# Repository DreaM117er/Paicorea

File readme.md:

# Paicorea

|||
|--|--|
|||

## 說明

Paicorea是一把專門為我而設計的分離式機械鍵盤，目的是為了讓鍵盤可以達到極度輕薄，又可以搭載`TPS43`這張由`Azoteq`公司生產製造的觸控板，滿足我的日常生活而使用。

它可以根據自己的需求選擇是否觸控板作為滑鼠使用；鍵盤按鍵則是使用`Kailh`生產製造的`PG1316S`作為它「目前」的按鍵使用，往後不排除會設計另一種機械鍵軸的版本來給自己做使用。

鍵盤的最初設計是像[AZCARD](https://github.com/palette-system/azcard)、[Bayleaf](https://kbd.news/Bayleaf-2610.html)、[Makefive](https://github.com/mikeholscher/zmk-config-mikefive)等一樣搭載`PG1316S`鍵軸的鍵盤都是以本體PCB作為底板壓縮厚度到3mm左右，但因為本人——也就是我自己，非常不喜歡使用無線設備（電池安全問題）的原因，一定得在鍵盤上搭載分離式鍵盤常見的`3.5mm TRRS座`，而我在這部分花了很多時間尋找能使用的零件，最後找到`PJ-381B`、`PJ-381C`、`PJ-399`等3款可以使用的沉板型號，再根據Datasheet跟3D設計，選擇了`PJ-381B`來使用。

在不想向下更換`2.5mm TRRS座`的前提下，很可惜地我只能將鍵盤厚度壓縮至5.5mm左右，但整體的結構讓我相當滿意。

使用`RP2040 Core-A`的原因——它跟用排線分離設計的`RP2040-Tiny`不同，我可以直接在PCB上拉USB2.0使用的USB-C口接線接在`RP2040 Core-A`上達到分離MCU跟USB-C的目的，而不用而外設計一個專門放置排線跟分離板的位置，而且又是厚度只有5.5mm的空間內。

最終從MCU——RP2040 Core-A（Raspberry Pi）中取Pi（π，Pai同音）、Core-A（corea），Paicorea就這麼誕生了。

## 使用材料

|名稱|規格|數量|備註|
|--|--|--|--|
|MCU|RP2040 Core-A|2|[Aliexpress Link](https://es.aliexpress.com/item/1005006101790601.html?channel=twinner)|
|Type-C母座|TYPE-C 16P CB1.6|2|沉板1.6mm|
|TRRS母座|PJ-381B|2|-|
|二極體|1N4148 `SOD-123`|42|-|
|貼片電阻|5.1K、`0603`|4|焊接後可支援C2C|
|鍵軸|Kailh PG1316S|42|-|
|鍵帽|適用PG1316S、`1u`大小|42|推薦用買的，3D列印需`留意邊角`圓弧|
|貼片銅柱|MAC8 TH0.8-2.0-M2（2.0）|16|-|
|貼片銅柱|MAC8 TH1.6-2.0-M2（2.0）|8|-|
|M2螺絲|牙長5mm、頭部`小於`ø4.2mm|24|-|
|矽膠自黏腳貼|ø8mm、厚度0.5-1.0mm|-|根據自己所需決定數量|
|緩衝墊|厚度0.5-0.8mm|-|矽膠或Poron等緩衝材料；需要裁切大小，請自行判斷需要多大面積|
|PVC板材|厚度0.8mm|-|觸控板面用，`A4`大小即可，需要裁切|
|0.5mm FFC排線座|6Pin|1|選配，安裝觸控板才需要|
|0.5mm FFC軟排線|6Pin、50mm、`AA同向`|1|選配，安裝觸控板才需要|
|觸控板|Azoteq TPS43-201A-S|1|選配|
|貼片LED燈|SK6805-2427（Micro）|6|選配，裝飾燈|

## 鍵盤結構

|||
|--|--|

|順序|部件|厚度（mm）|備註|
|--|--|--|--|
|1|上蓋-A（Cover-A）、觸控板邊框-A（Track-A）|1.6|有無觸控板做選擇|
|2|上蓋-B（Cover-B）、觸控板邊框-B（Track-B）|0.8|有無觸控板做選擇|
|3|定位板（Plate）|0.8|-|
|4|間隙空間板（Body）|1.6|-|
|5|核心電路板（Main）|1.6|-|
|6|緩衝層（Frame）|0.5-0.8|自行裁切或使用電路板層都可|
|7|底板（Bottom）|0.8|-|

## 使用工具

||名稱|使用場合|備註|
|--|--|--|--|
|1|電烙鐵|基本電路板焊接|修正焊錫使用，推薦使用K頭（刀頭）|
|2|熱風槍或加熱台|進階電路板焊接|擇一使用即可|
|3|針筒裝錫膏|進階電路板焊接||
|4|剪刀及美工刀|裁切膠帶及塑料板材||
|5|超薄超黏雙面膠|粘貼固定觸控板用|0.13-0.15mm厚度的即可|
|6|對應電路板顏色的簽字筆|邊框填色使用|可不需使用|
|7|防靜電金屬鑷子|進階電路板焊接、測試、精密操作||
|8|精密螺絲起子|-|對應螺絲規格使用|
|9|平口老虎鉗|分離拼接電路板時使用||
|10|銼刀|打磨電路板邊框時用||
|11|皮革打洞器|裁切矽膠墊使用|需要打ø4-4.5mm的孔|
|12|鉛筆或原子筆|裁切PVC塑膠板時使用||
|13|3秒膠或AB膠|固定層板使用||

## 組裝說明

### 注意事項

- 務必將所有元件都焊接在同一面。
- 焊接MCU、二極體、鍵軸及LED燈等... 都務必都要進行測試再做下一步動作。
- 只要有安裝方向的元件都會標示在電路板上，反之沒有安裝方向的元件什麼都不會標記。
- MCU上的THT焊盤孔用作定位使用。
- 使用焊接工具時務必注意安全，小心燙傷。

### 安裝順序

|圖示|說明|
|--|--|
||首先將`MCU`、`USB-C`接口、`5.1K`電阻及`FFC`排線座焊接好。|
||連接電腦測試MCU的狀態，如果順利接通MCU的話，MCU上面的`橘紅色LED燈`會閃爍。|
||請根據RP2040的燒錄方式將韌體燒錄至MCU，成功的話LED燈會亮，還有VIAL會成功讀取到鍵盤。|
||再來焊接TRRS座。|
||接著按照順序將`1N4148`及`PG1316S`焊接起來，PG1316S的燈光孔是可以容下1N4148的，務必將二極體包覆在軸燈燈孔裡面。|
||然後將貼片銅柱（`MAC8 TH1.6-2.0-M2`）焊接上去。|
||接著將另一側鍵盤也焊好。|
||再來將底板（Bottom）的貼片銅柱（`MAC8 TH0.8-2.0-M2`）也焊接固定好。|
||接著依照底板（Bottom）、緩衝層（Frame）、電路板（Main）、間隙（Body）、定位板（Plate）的順序將鍵盤疊好，再把鍵盤外側的螺絲鎖上去固定。|
||將Cover-A、Cover-B、Track-A、Track-B用工具剝下來。|
||然後將其中一側的Cover蓋起來用螺絲鎖好，完成其中一邊，如果不需要安裝觸控板就把兩側鍵盤都鎖上Cover就完成了。|
||觸控板的部分可以選擇使用列印或自己切觸控板Cover。|
||首先將觸控板上的3M貼紙撕下來貼在8mm的PVC板材上後裁切下來，再把多餘的邊切除。|
||好了之後將Track-A固定好，貼上超黏雙面膠。|
||一樣切除多餘的膠。|
||撕下膠的另一面之後，將A、B合併在一起。|
||接上排線，稍微彎折收納一下排線。|
||鎖上螺絲。|
||然後翻到背面貼上腳貼或自行DIY上Tending。|
||安裝鍵帽之後就完成啦。|

## 參考資料

### 鍵盤
- [AZCARD](https://github.com/palette-system/azcard)：結構部分及銅柱元件參照。
- [Makefive](https://github.com/mikeholscher/zmk-config-mikefive)：結構部分。
- [Bayleaf](https://kbd.news/Bayleaf-2610.html)：結構部分。
- [Corne v4](https://github.com/foostan/crkbd)：TRRS連接座、PCB走線參照。
- [X：おおやけハジメ](https://x.com/digitarhythm)——[未完成"V1"](https://x.com/digitarhythm/status/1908885665695363132)：
PCB走線參照。

### 部落格、網頁、參考說明書
- [Holykeeb](https://holykeebs.com/)、[Holykeeb.Docs](https://docs.holykeebs.com/guides/touchpad-module/)。
- [74th Blog](https://74th.hateblo.jp/entry/testing-TPS43-201A-S)
- [Reddit: mikefive, a Kailh PG1316 keyboard](https://www.reddit.com/r/ErgoMechKeyboards/comments/1cfg3vr/mikefive_a_kailh_pg1316_keyboard/)
- [KBD.News](https://kbd.news/)

### 規格書
- PJ-381B、PJ-381-C、PJ-399。
- TYPE-C 16P CB1.6。
- MAC8 THXX-XX-M2。
- SK6805-2427。
- Kailh PG1316S & Keycap。
- Azoteq TPS43-201A-S。

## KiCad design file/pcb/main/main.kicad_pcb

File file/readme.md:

## 注意事項

- 公差設定0.05mm。
- 3D模型由於沒有變更太多東西，相容性不影響，因此我就沒有更新新的上去了。
- 結構為標準電路板堆疊，因此才能夠將鍵盤壓縮至10mm以內。
- 底板經過Prototype測試，厚度不允許從1.6mm降低至0.8mm，TRRS線會摩擦桌面，實際使用上會有問題。
- 裁切能力有限的夥伴，請一律定製電路板外殼來製作鍵盤，厚度不會差異太多。

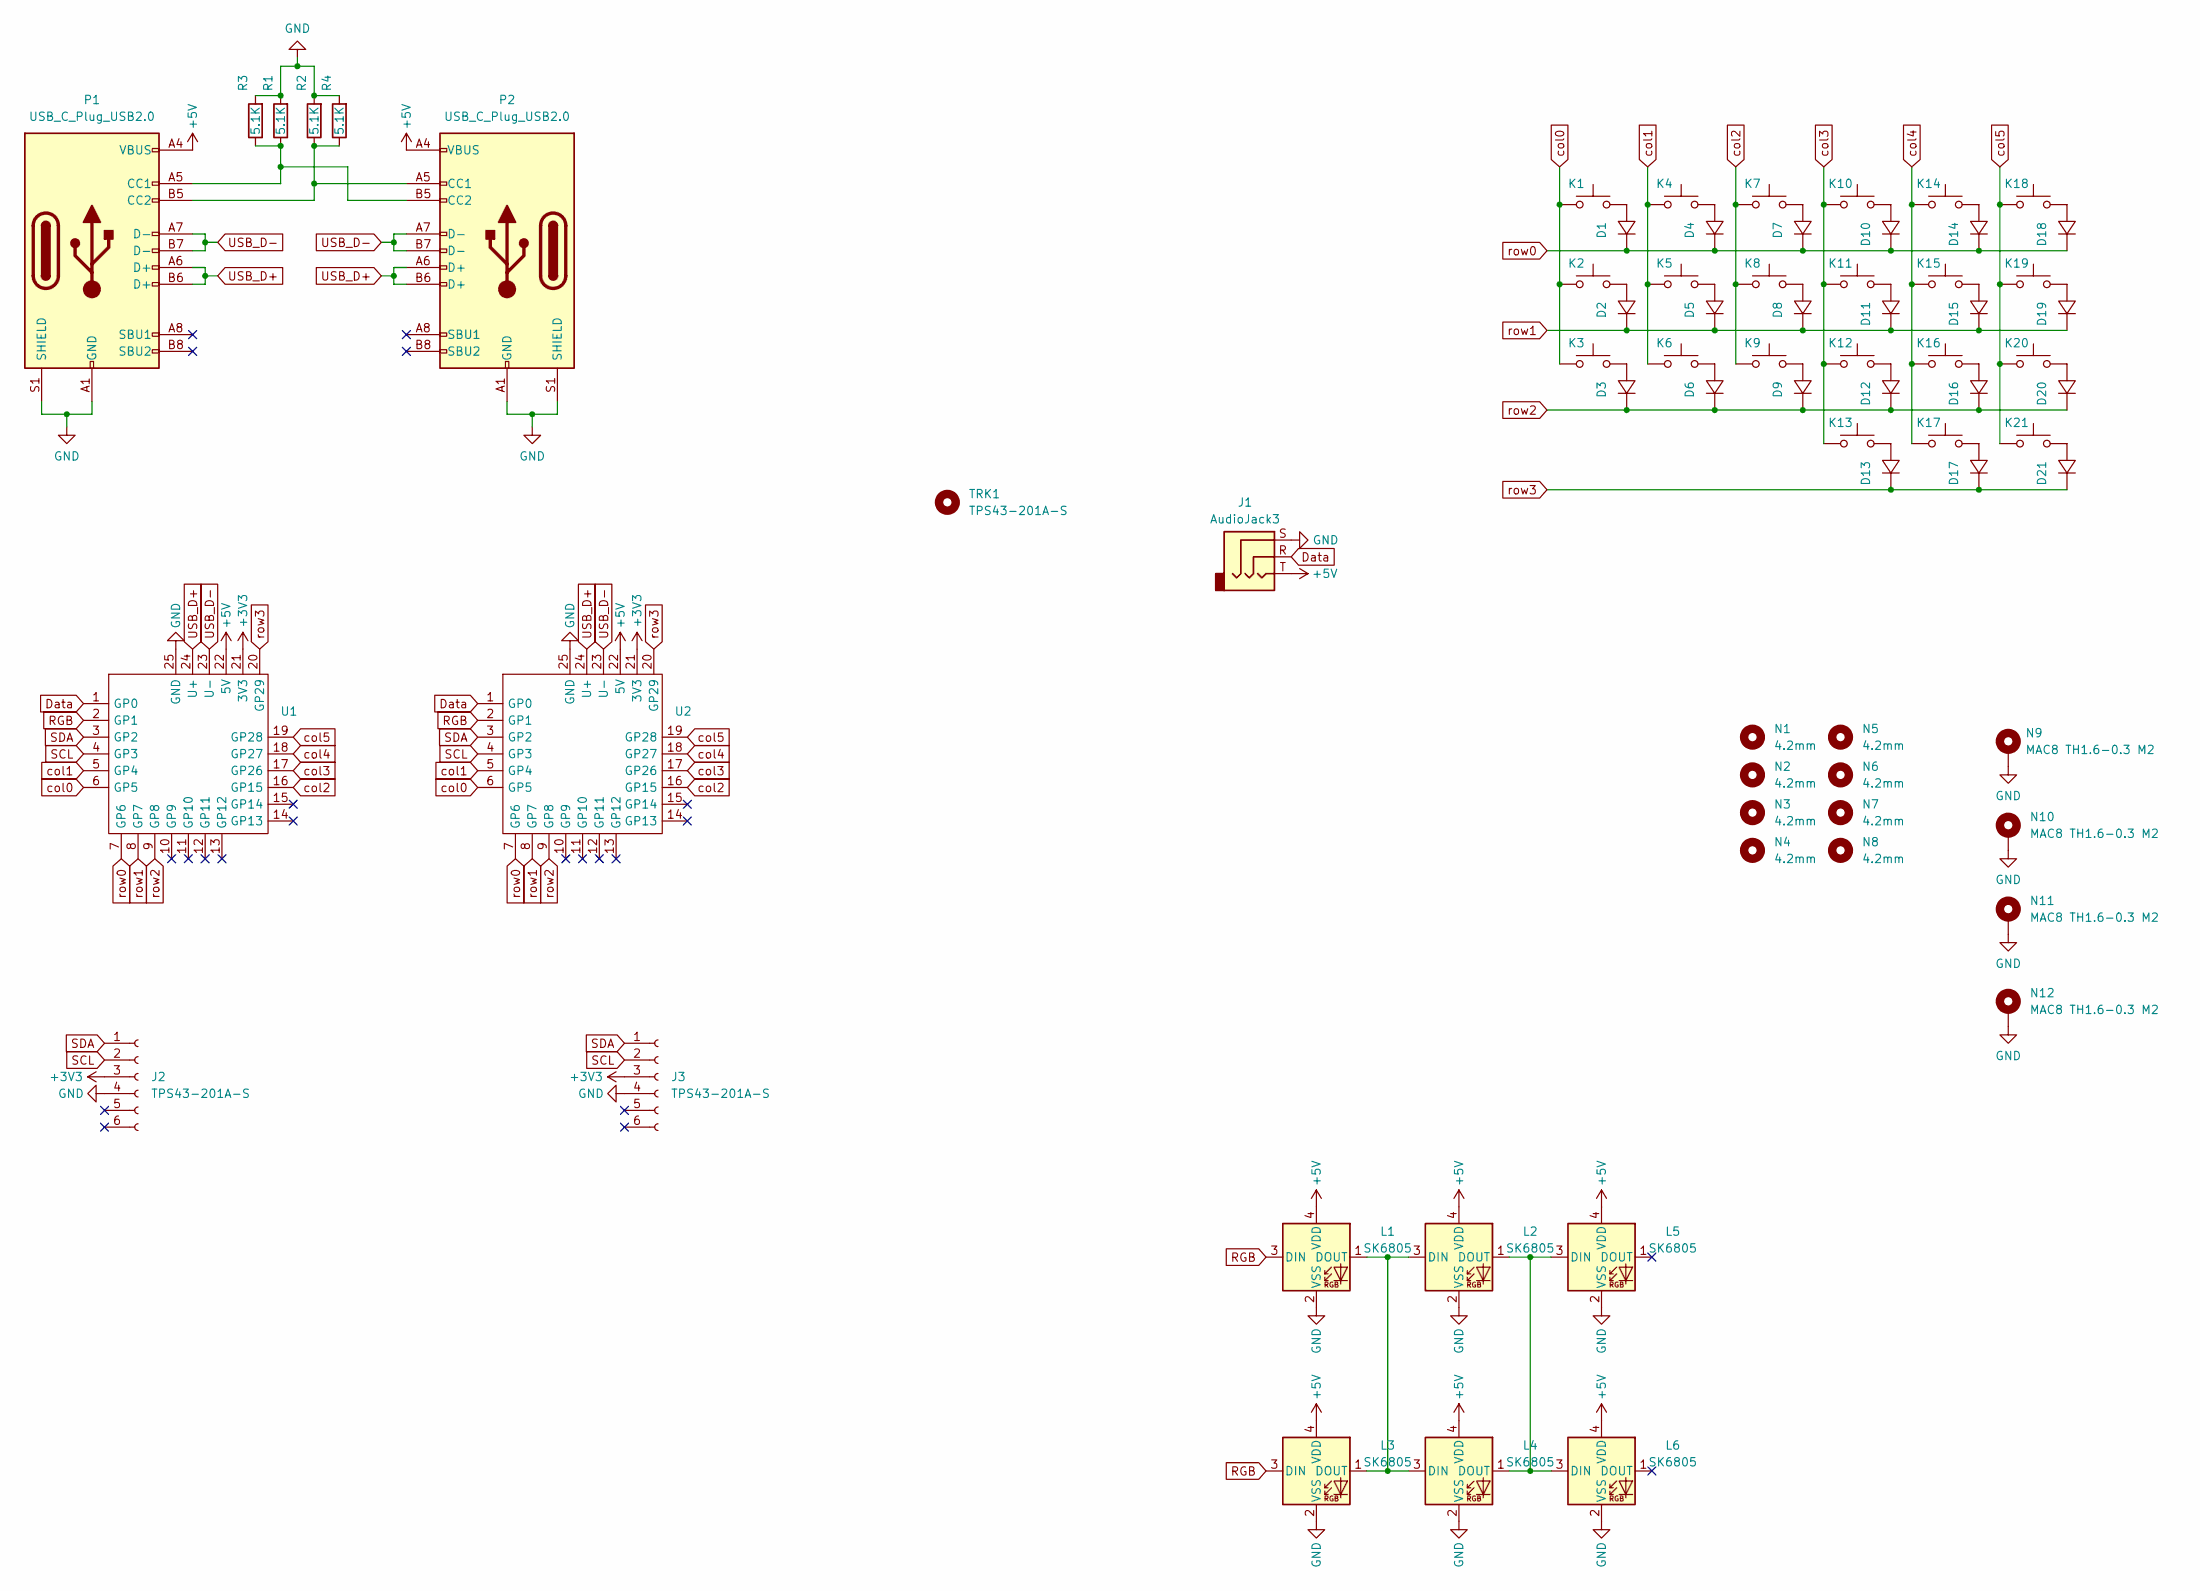
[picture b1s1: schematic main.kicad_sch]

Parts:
D1, D2, D3, D4, D5, D6, D7, D8, D9, D10, D11, D12, D13, D14, D15, D16, D17, D18, D19, D20, D21: 1N4148_SMD; D_SOD-123_dual
J1: AudioJack3; TRRS-PJ-381-BB_6P_Dual
J2, J3: TPS43-201A-S; Hirose_FH12-6S-0.5SH_1x06-1MP_P0.50mm_Horizontal
K1, K2, K3, K4, K5, K6, K7, K8, K9, K10, K11, K12, K13, K14, K15, K16, K17, K18, K19, K20, K21: PG1316S; SW_Kailh_PG1316S_1.00u_Dual2
L1, L2, L3, L4, L5, L6: SK6805; LED_SK6805_PLCC4_2.4x2.7mm_P1.3mm
N1, N2, N3, N4, N5, N6, N7, N8: 4.2mm; MAC8_TH0816-XX-M2-NPTHhole
N9, N10, N11, N12: MAC8 TH1.6-0.3 M2; MAC8_TH0816-XX-M2-Dual_Pad
P1, P2: USB_C_Plug_USB2.0; USB_C_16P_MID_MOUT_SR_Molex
R1, R2, R3, R4: 5.1K; R_0603_1608Metric
TRK1: TPS43-201A-S; Azoteq_TPS43_201A_S
U1, U2: MCU_RP2040_CoreA_SMD; MCU_RP2040CoreA_SMD

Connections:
+3V3: J2.3, J3.3, U1.21 (3V3), U2.21 (3V3)
+5V: J1.T, L1.4 (VDD), L2.4 (VDD), L3.4 (VDD), L4.4 (VDD), L5.4 (VDD), L6.4 (VDD), P1.A4 (VBUS), P1.A9 (VBUS), P1.B4 (VBUS), P1.B9 (VBUS), P2.A4 (VBUS), P2.A9 (VBUS), P2.B4 (VBUS), P2.B9 (VBUS), U1.22 (5V), U2.22 (5V)
Data: J1.R, U1.1 (GP0), U2.1 (GP0)
GND: J1.S, J2.4, J3.4, L1.2 (VSS), L2.2 (VSS), L3.2 (VSS), L4.2 (VSS), L5.2 (VSS), L6.2 (VSS), N9.1, N10.1, N11.1, N12.1, P1.A1 (GND), P1.A12 (GND), P1.B1 (GND), P1.B12 (GND), P1.S1 (SHIELD), P2.A1 (GND), P2.A12 (GND), P2.B1 (GND), P2.B12 (GND), P2.S1 (SHIELD), R1.2, R2.2, R3.2, R4.2, U1.25 (GND), U2.25 (GND)
unnamed: D1.2, K1.2
unnamed: D2.2, K2.2
unnamed: D3.2, K3.2
unnamed: D4.2, K4.2
unnamed: D5.2, K5.2
unnamed: D6.2, K6.2
unnamed: D7.2, K7.2
unnamed: D8.2, K8.2
unnamed: D9.2, K9.2
unnamed: D10.2, K10.2
unnamed: D11.2, K11.2
unnamed: D12.2, K12.2
unnamed: D13.2, K13.2
unnamed: D14.2, K14.2
unnamed: D15.2, K15.2
unnamed: D16.2, K16.2
unnamed: D17.2, K17.2
unnamed: D18.2, K18.2
unnamed: D19.2, K19.2
unnamed: D20.2, K20.2
unnamed: D21.2, K21.2
unnamed: L1.1 (DOUT), L2.3 (DIN), L3.1 (DOUT), L4.3 (DIN)
unnamed: L2.1 (DOUT), L4.1 (DOUT), L5.3 (DIN), L6.3 (DIN)
unnamed: P1.A5 (CC1), P2.B5 (CC2), R1.1, R3.1
unnamed: P1.B5 (CC2), P2.A5 (CC1), R2.1, R4.1
RGB: L1.3 (DIN), L3.3 (DIN), U1.2 (GP1), U2.2 (GP1)
SCL: J2.2, J3.2, U1.4 (GP3), U2.4 (GP3)
SDA: J2.1, J3.1, U1.3 (GP2), U2.3 (GP2)
USB_D+: P1.A6 (D+), P1.B6 (D+), P2.A6 (D+), P2.B6 (D+), U1.24 (U+), U2.24 (U+)
USB_D-: P1.A7 (D-), P1.B7 (D-), P2.A7 (D-), P2.B7 (D-), U1.23 (U-), U2.23 (U-)
col0: K1.1, K2.1, K3.1, U1.6 (GP5), U2.6 (GP5)
col1: K4.1, K5.1, K6.1, U1.5 (GP4), U2.5 (GP4)
col2: K7.1, K8.1, K9.1, U1.16 (GP15), U2.16 (GP15)
col3: K10.1, K11.1, K12.1, K13.1, U1.17 (GP26), U2.17 (GP26)
col4: K14.1, K15.1, K16.1, K17.1, U1.18 (GP27), U2.18 (GP27)
col5: K18.1, K19.1, K20.1, K21.1, U1.19 (GP28), U2.19 (GP28)
row0: D1.1, D4.1, D7.1, D10.1, D14.1, D18.1, U1.7 (GP6), U2.7 (GP6)
row1: D2.1, D5.1, D8.1, D11.1, D15.1, D19.1, U1.8 (GP7), U2.8 (GP7)
row2: D3.1, D6.1, D9.1, D12.1, D16.1, D20.1, U1.9 (GP8), U2.9 (GP8)
row3: D13.1, D17.1, D21.1, U1.20 (GP29), U2.20 (GP29)

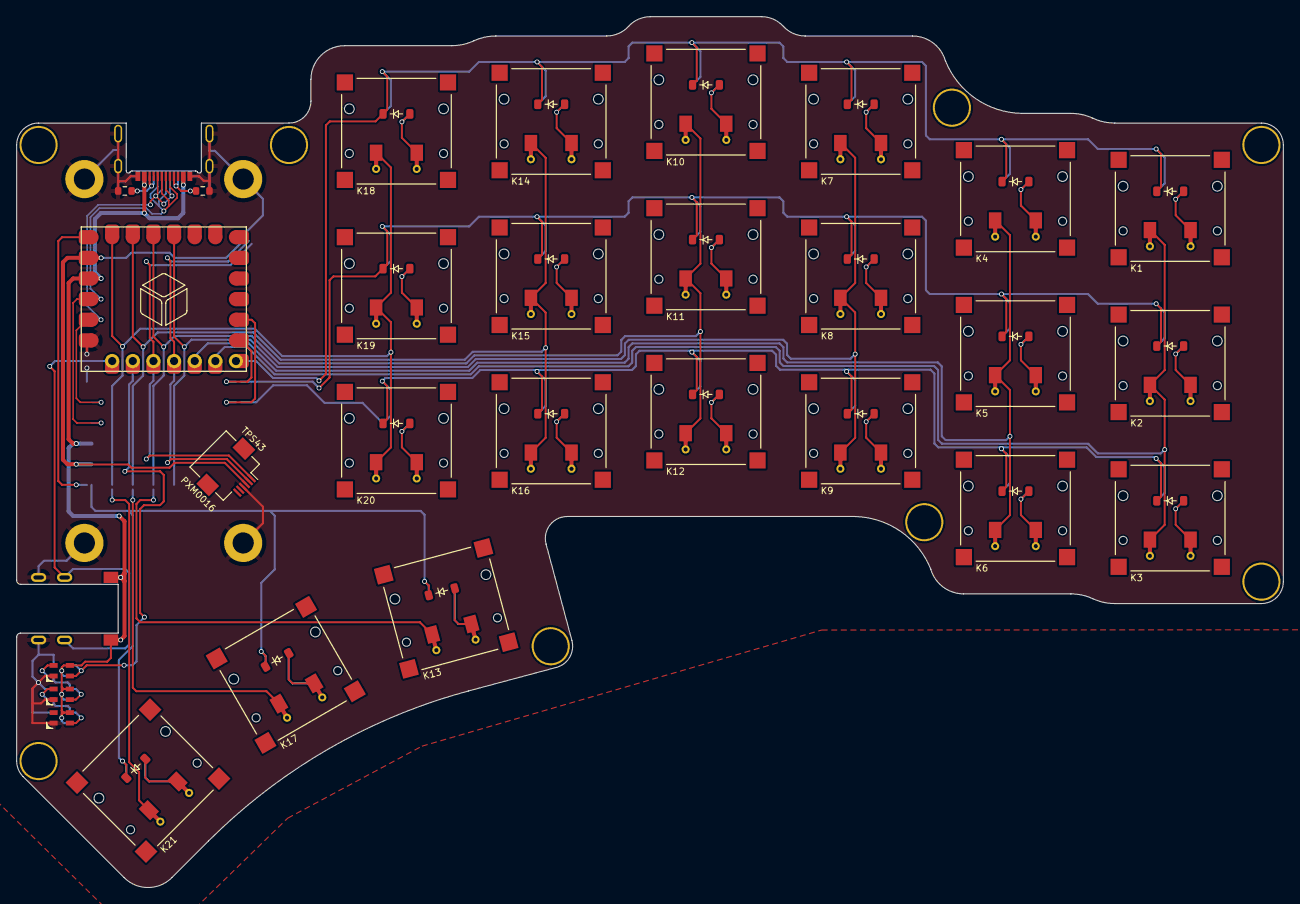
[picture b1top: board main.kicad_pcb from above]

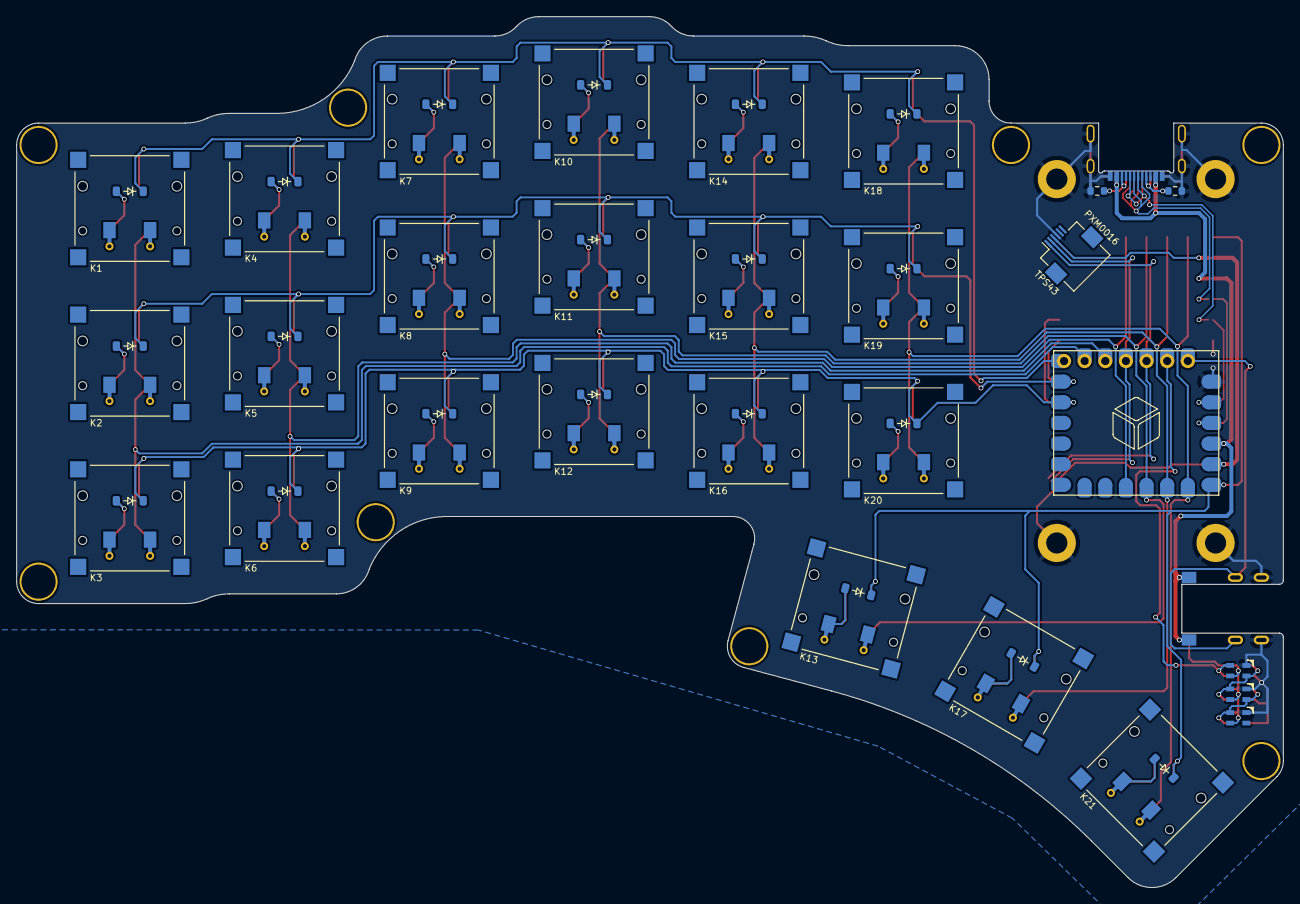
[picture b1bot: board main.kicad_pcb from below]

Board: 2 copper layers, 155.9 x 107.2 mm, 72 parts (8 on the bottom side), 44 nets.

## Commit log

2025-04-18 update info
2025-04-19 update datasheet file
2025-04-20 update 3d & pcb files
2025-04-24 add rgb file
2025-04-29 update prototype files
2025-04-29 set the new files
2025-04-29 update new LED layout
2025-04-29 update frame
2025-05-28 update building guide
2025-05-28 resize pic
2025-05-28 fix text in readme
2025-05-29 fix text in readme.md
